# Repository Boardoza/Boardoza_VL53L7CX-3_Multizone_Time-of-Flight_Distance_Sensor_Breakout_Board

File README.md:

# Boardoza VL53L7CX-3 Time-of-Flight Breakout Board

The **Boardoza VL53L7CX-3 Time-of-Flight Breakout Board** is a compact distance sensing solution built around the **STMicroelectronics VL53L7CX** multizone Time-of-Flight (ToF) sensor. The sensor combines a **940 nm invisible VCSEL emitter** and a **SPAD receiving array** to deliver accurate distance measurements across a configurable **4×4 or 8×8 ranging zone matrix**, providing up to **64 independent zones**.

Designed specifically for **3.3V to 5V powered systems**, this breakout board integrates a low-dropout voltage regulator and level-shifting circuitry for I²C communication and interrupt signaling.This enables direct connection to both 3.3V and 5V microcontroller systems while providing the required operating voltage for the sensor. The board also provides extra control functions such as interrupt output (INT), communication enable control (LPn), and I²C interface reset (RST). Its dual-connector layout also allows multiple boards to be connected in a **cascade connection**, making it easier to use more than one VL53L7CX board on the same I²C bus. Typical applications include **robotics, occupancy detection, gesture recognition, obstacle avoidance, smart appliances, industrial automation, and embedded sensing applications** where compact size and reliable ranging performance are required.

## [Click here to purchase!](https://www.ozdisan.com/p/moduller-870/boardoza-vl53l7cx-3-1577677?s=VL53L7CX-3)

| Front Side | Back Side |
| :---: | :---: |
|  |  |

---

## Key Features

- **Multizone Distance Sensing:** Supports both 4×4 and 8×8 ranging configurations, providing up to 64 independent measurement zones.
- **Ultra-Wide Field of View:** Provides a 60° × 60° square detection FoV with a 90° diagonal field of view.
- **3.3V–5V System Compatible:** Supports a 3.3V to 5V supply input with onboard voltage regulation.
- **Level-Shifted Communication and Interrupt Lines:** SDA, SCL, and INT lines include level shifting for compatibility with 3.3V and 5V microcontroller systems.
- **3.3V Control Signals:** RST and LPn pins operate at 3.3V logic level and should not be driven with 5V signals.
- **Eye-Safe Operation:** Integrated Class 1 invisible 940nm VCSEL (Vertical-Cavity Surface-Emitting Laser) emitter is safe for the eyes and enables safe operation in consumer and industrial products.
- **Multitarget Detection:** Capable of detecting and measuring multiple targets within each ranging zone.
- **Autonomous Low-Power Mode:** Supports autonomous operation with programmable interrupt thresholds for host wake-up applications.
- **Power Status Indicator:** Integrated LED provides visual confirmation of power availability.

---

## Technical Specifications

**Model:** VL53L7CX-3  
**Manufacturer:** Boardoza  
**Manufacturer IC:** STMicroelectronics     
**Function:** Multizone Time-of-Flight (ToF) Distance Sensor  
**Board Supply Voltage:** 3.3V to 5V  
**Onboard Regulation:** 3.3V LDO Regulator  
**Communication Interface:** I²C  
**I²C Address:** 0x52 (8-bit address)  
**Maximum I²C Speed:** 1 Mbit/s  
**Ranging Zones:** 4 × 4 or 8 × 8, up to 64 zones  
**Maximum Sampling Rate:** Up to 60Hz  
**Measurement Range:** 2cm to 350cm per zone  
**Field of View:** 60° × 60° detection FoV, 90° diagonal  
**Emitter Type:** 940nm invisible VCSEL (Vertical-Cavity Surface-Emitting Laser)  
**Detector Type:** SPAD (Single Photon Avalanche Diode) receiving array  
**Safety Classification:** Class 1 Eye-Safe  
**Logic Levels:** 5V compatible on SDA, SCL, and INT; 3.3V on RST and LPn  
**Operating Temperature:** -30°C to +85°C  
**Board Dimensions:** 20mm × 20mm  

---

## Model Comparison

All four boards use the same **STMicroelectronics VL53L7CX multizone Time-of-Flight sensor** and provide the same core ranging capabilities. The main differences between the models are their **supply voltage requirements** and the signals on which **logic-level shifting** is provided.

|      Model     | Board Supply Input | Onboard 3.3V Regulator | 5V-Compatible Signals | Native 3.3V Signals     | Practical Difference                                                                                                                                                                                             | Recommended Use                                                                                             |
| :------------: | :----------------: | :--------------------: | :-------------------- | :---------------------- | ---------------------------------------------------------------------------------------------------------------------------------------------------------------------------------------------------------------- | ----------------------------------------------------------------------------------------------------------- |
| **VL53L7CX-1** |        3.3V        |           No           | None                  | SDA, SCL, INT, RST, LPn | The entire board operates directly from 3.3V. No voltage regulation or logic-level shifting is included. All connected signals must remain at 3.3V.                                                              | Best for systems in which both the power supply and the microcontroller logic operate at 3.3V.              |
| **VL53L7CX-2** |     3.3V to 5V     |           Yes          | SDA, SCL              | INT, RST, LPn           | The board can be powered from either 3.3V or 5V. The I²C communication lines are level-shifted, allowing SDA and SCL to communicate with both 3.3V and 5V hosts. The control signals remain at 3.3V logic level. | Best when the host uses 5V I²C communication but the INT, RST, and LPn control pins can be handled at 3.3V. |
| **VL53L7CX-3** |     3.3V to 5V     |           Yes          | SDA, SCL, INT         | RST, LPn                | In addition to the I²C lines, the interrupt output is also level-shifted. This allows the host to receive the INT signal at its own logic voltage. RST and LPn still operate at 3.3V.                            | Best when both I²C communication and the interrupt signal need to be compatible with a 5V microcontroller.  |
| **VL53L7CX-4** |         3.3V to 5V         |           Yes          | None                  | SDA, SCL, INT, RST, LPn | The board is powered from 5V, but all communication and control signals remain at native 3.3V logic levels. The connected host must therefore use 3.3V-compatible I/O signals.                                   | Best for systems that provide a 5V power rail but use a 3.3V microcontroller or 3.3V host interface.        |

### How to Select the Right Model

* Choose **VL53L7CX-1** when the complete system operates at **3.3V**.
* Choose **VL53L7CX-2** when you need **3.3V–5V compatible I²C communication**, but the control pins can remain at 3.3V.
* Choose **VL53L7CX-3** when both the **I²C lines and the INT output** must be compatible with a 5V host.
* Choose **VL53L7CX-4** when the board will be powered from **3.3V-5V**, but the connected microcontroller uses **3.3V logic**.

> **Important Note:** A board being powered from 5V does not automatically mean that all of its communication and control pins can accept 5V logic signals. Always check the logic-level compatibility of SDA, SCL, INT, RST, and LPn before connecting the board to a host system.

### Common Features of All Four Models

The following features are identical across all four models:

* STMicroelectronics VL53L7CX multizone Time-of-Flight sensor
* 4×4 or 8×8 ranging configurations
* Up to 64 independent measurement zones
* 60° × 60° square detection field of view
* 90° diagonal field of view
* Up to 60Hz ranging frequency
* Multitarget detection within each zone
* I²C communication
* INT, RST, and LPn control functions
* Class 1 eye-safe 940nm VCSEL emitter
* Dual-connector layout for easier multi-board connection

---

## Board Pinout

### ( J1 ) Power & I²C Connector

| Pin Number | Pin Name | Description |
| :---: | :---: | --- |
| 1 | GND | Ground |
| 2 | SCL | I²C Serial Clock |
| 3 | SDA | I²C Serial Data |
| 4 | 5V | Positive Power Supply |

### ( J2 ) Control & I²C Connector

| Pin Number | Pin Name | Description |
| :---: | :---: | --- |
| 1 | 5V | Positive Power Supply |
| 2 | GND | Ground |
| 3 | SDA | I²C Serial Data |
| 4 | SCL | I²C Serial Clock |
| 5 | RST | I²C interface reset input, active high. Toggle from Low to High and back to Low to reset the I²C target interface only. Operates at 3.3V logic level. |
| 6 | INT | Level-shifted interrupt output. Used to notify the host when ranging data or threshold events are available. |
| 7 | LPn | Communication enable input. Pulled up to 3.3V for normal operation; drive Low to disable I²C communication. |

---

## Board Dimensions

---

## Step Files

[Boardoza VL53L7CX-3.step](./assets/VL53L7CX-3%20Step.step)

---

## Datasheet

[VL53L7CX Datasheet.pdf](./assets/VL53L7CX-3%20Datasheet.pdf)

---

## Version History

- V1.0.0 - Initial Release

---

## Support

- If you have any questions or need support, please contact <support@boardoza.com>

---

## **License**

This repository contains both hardware and software components:

### **Hardware Design**

[![CC BY-SA 4.0][cc-by-sa-shield]][cc-by-sa]

All hardware design files are licensed under [Creative Commons Attribution-ShareAlike 4.0 International License][cc-by-sa].

[cc-by-sa]: http://creativecommons.org/licenses/by-sa/4.0/
[cc-by-sa-shield]: https://img.shields.io/badge/License-CC%20BY--SA%204.0-lightgrey.svg

### **Software/Firmware**

[![BSD-3-Clause][bsd-shield]][bsd]

All software and firmware are licensed under [BSD 3-Clause License][bsd].

[bsd]: https://opensource.org/licenses/BSD-3-Clause
[bsd-shield]: https://img.shields.io/badge/License-BSD%203--Clause-blue.svg

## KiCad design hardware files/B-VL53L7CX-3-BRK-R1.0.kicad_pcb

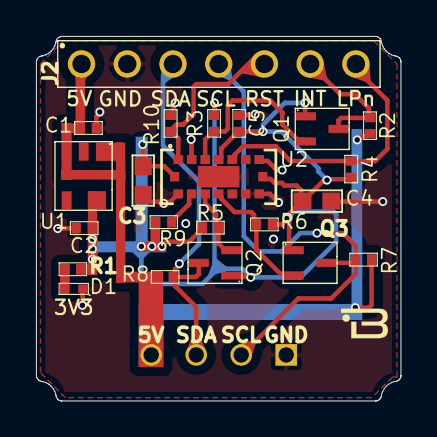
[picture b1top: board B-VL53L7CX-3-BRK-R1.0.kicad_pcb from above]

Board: 2 copper layers, 20.3 x 20.3 mm, 23 parts (1 on the bottom side), 13 nets.

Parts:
C1, C2: UMK105CBJ105KV-F; CAP 0402
C3, C4: CL10A475KP8NNNC; CAP 0603
C5: GRM155R71H104KE14D; CAP 0402
D1: 16-213SURC/S530-A3/TR8; LED 0402
J1: L-KLS1-2.50-04-S; 22035045
J2: L-KLS1-207-2.50-1-07-S; PIN Header
Q1, Q2, Q3: BSS138W-7-F; SOT-323
R1: 0402WGJ0201TCE; RES 0402
R2, R3, R4, R9, R10: CQ02WGJ0473TCE; RES 0402
R5, R6, R7, R8: 0402WGF2201TCE; RES 0402
U1: AP2112K-3.3TRG1; SOT-25
U2: VL53L5CXV0GC1; VL53L5CX LGA_CXV0GC1_STM

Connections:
3V3: C2.2, C3.1, C4.1, C5.2, Q1.1, Q2.1, Q3.1, R1.2, R3.2, R4.2, R5.2, R6.2, R9.1, U1.5, U2.A4, U2.B1, U2.B7
5V: C1.2, J1.4, J2.1, R2.2, R7.2, R8.2, U1.1, U1.3
GND: C1.1, C2.1, C3.2, C4.2, C5.1, D1.1, J1.1, J2.2, R10.1, U1.2, U2.17, U2.A2, U2.A6, U2.A7, U2.C1, U2.C6, U2.C7
I2C_RST: J2.5, R10.2, U2.A1
INT: J2.6, Q1.3, R2.1
LPn: J2.7, R4.1, U2.A5
NetD1_2: D1.2, R1.1
NetQ1_2: Q1.2, R3.1, U2.A3
NetQ2_2: Q2.2, R5.1, U2.C3
NetQ3_2: Q3.2, R6.1, U2.C4
NetR9_2: R9.2, U2.C2
SCL: J1.2, J2.4, Q3.3, R7.1
SDA: J1.3, J2.3, Q2.3, R8.1
